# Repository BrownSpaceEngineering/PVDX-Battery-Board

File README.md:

# Battery-Board

Battery subsystem board for PVDX — connects the battery stack, solar cells/solar PCB, heaters, and thermistors.

## Status
- Design phase: fabrication
- Current rev: rev-1.1
- Contributors: Jayla Hsiung, Kelly Lin, Finn Kehoe, Dean Zweiman

## System overview

The Battery Board is primarily structural/routing rather than active. It has no onboard charging or regulation ICs (that logic lives on EPS). Its job is to tie the battery stack into the rest of the power subsystem: routing to the regular (non-perovskite) solar cells and solar PCB, driving the battery heaters, and carrying thermistor signals back for battery temperature monitoring.

**Board sheets:**

- **Heater**: battery heater circuit.
- **Connectors**: harness/pinout for battery, solar, heater, and thermistor connections. These are being hardwired rather than connectorized — the footprints (pad patterns) stay on the board for wire attachment points, but the 3D models are hidden (Show unchecked in Footprint Properties → 3D Models) so they don't appear in the STEP export.

### Repo layout

```
PVDX-Battery-Board/
├── PVDX-Battery-Board.kicad_pro / .kicad_sch / .kicad_pcb
├── fp-lib-table
├── schematics/
│   ├── heater.kicad_sch
│   └── connectors.kicad_sch
├── libs/
│   ├── footprints.pretty/
│   ├── symbols/
│   └── 3d_models/
└── manufacturing/
    └── rev-<N>_<date>/
        ├── gerbers/
        ├── bom/
        └── plots/
```

**Why hardwire instead of connectors:** simplifies the harness at the battery/heater interface and removes a failure point (connector) from a joint that doesn't need to be serviceable in flight. KiCad has no dedicated "exclude from STEP" option, so per-footprint 3D model visibility is the mechanism used to keep the pad pattern without the connector body in mechanical exports.

## Key design notes

- **Thermistor (NXFT15XV103FEAB025):** custom footprint, kept in `libs/footprints.pretty/`. The original vendor export had a stray space in the filename — fixed during the repo reorg.
- **Connector footprints, 3D models hidden:** see above — keep an eye on this after any "Update PCB from Schematic" footprint refresh, which can reset visibility to the library default and re-show the model.
- **`PVDX_BatteryBoard_Board.kicad_sch`** was an orphaned, blank sheet not referenced anywhere in the hierarchy — deleted during the reorg.

## Manufacturing history
| Rev | Date | Notes | Location |
|-----|------|-------|----------|
| 1.1 | 8/22/26 | Current gerber set | `manufacturing/rev-1.1_2026-08-22/` |

## Open items
- Fill in BOM for rev-1.1 (`manufacturing/rev-1.1_2026-08-22/bom/` currently empty)

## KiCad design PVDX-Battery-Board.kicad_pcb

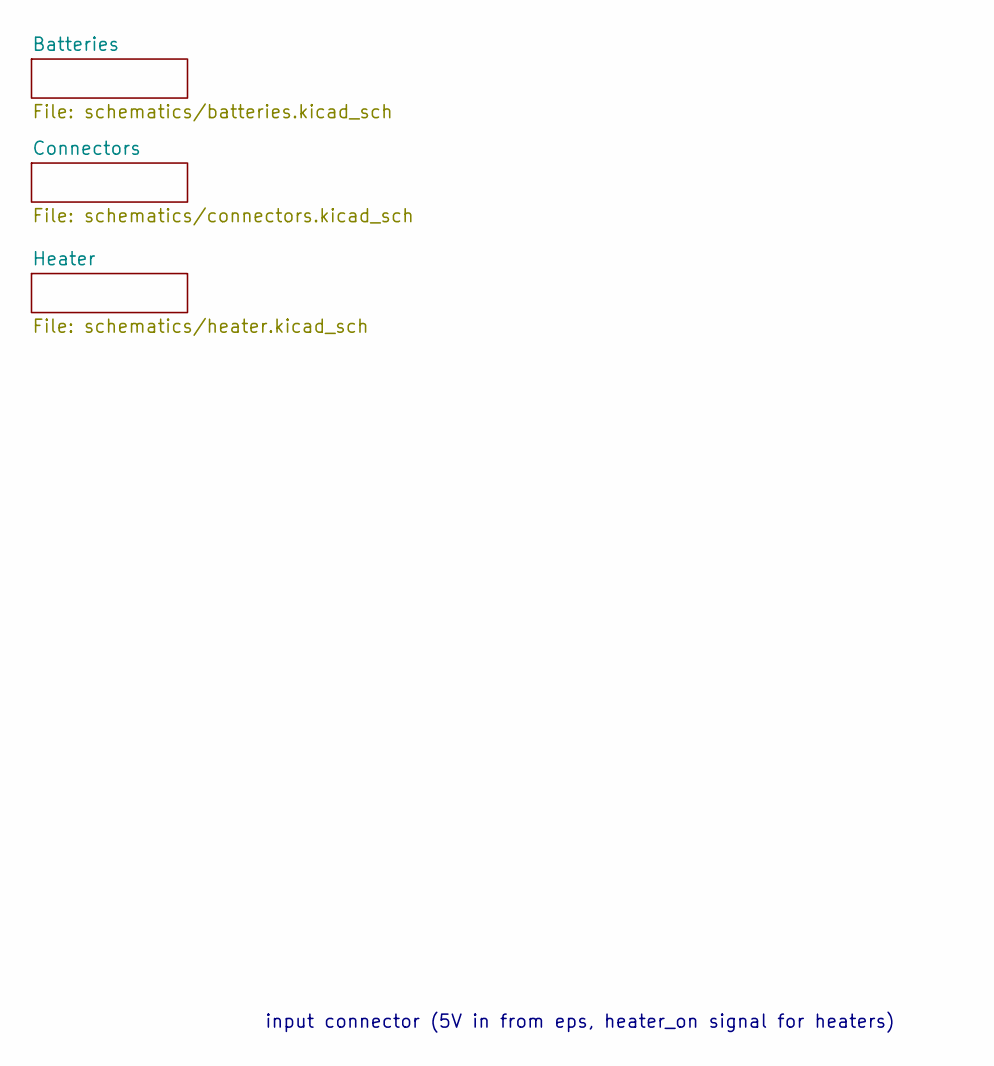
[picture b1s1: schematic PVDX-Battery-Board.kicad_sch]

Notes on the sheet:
input connector (5V in from eps, heater_on signal for heaters)

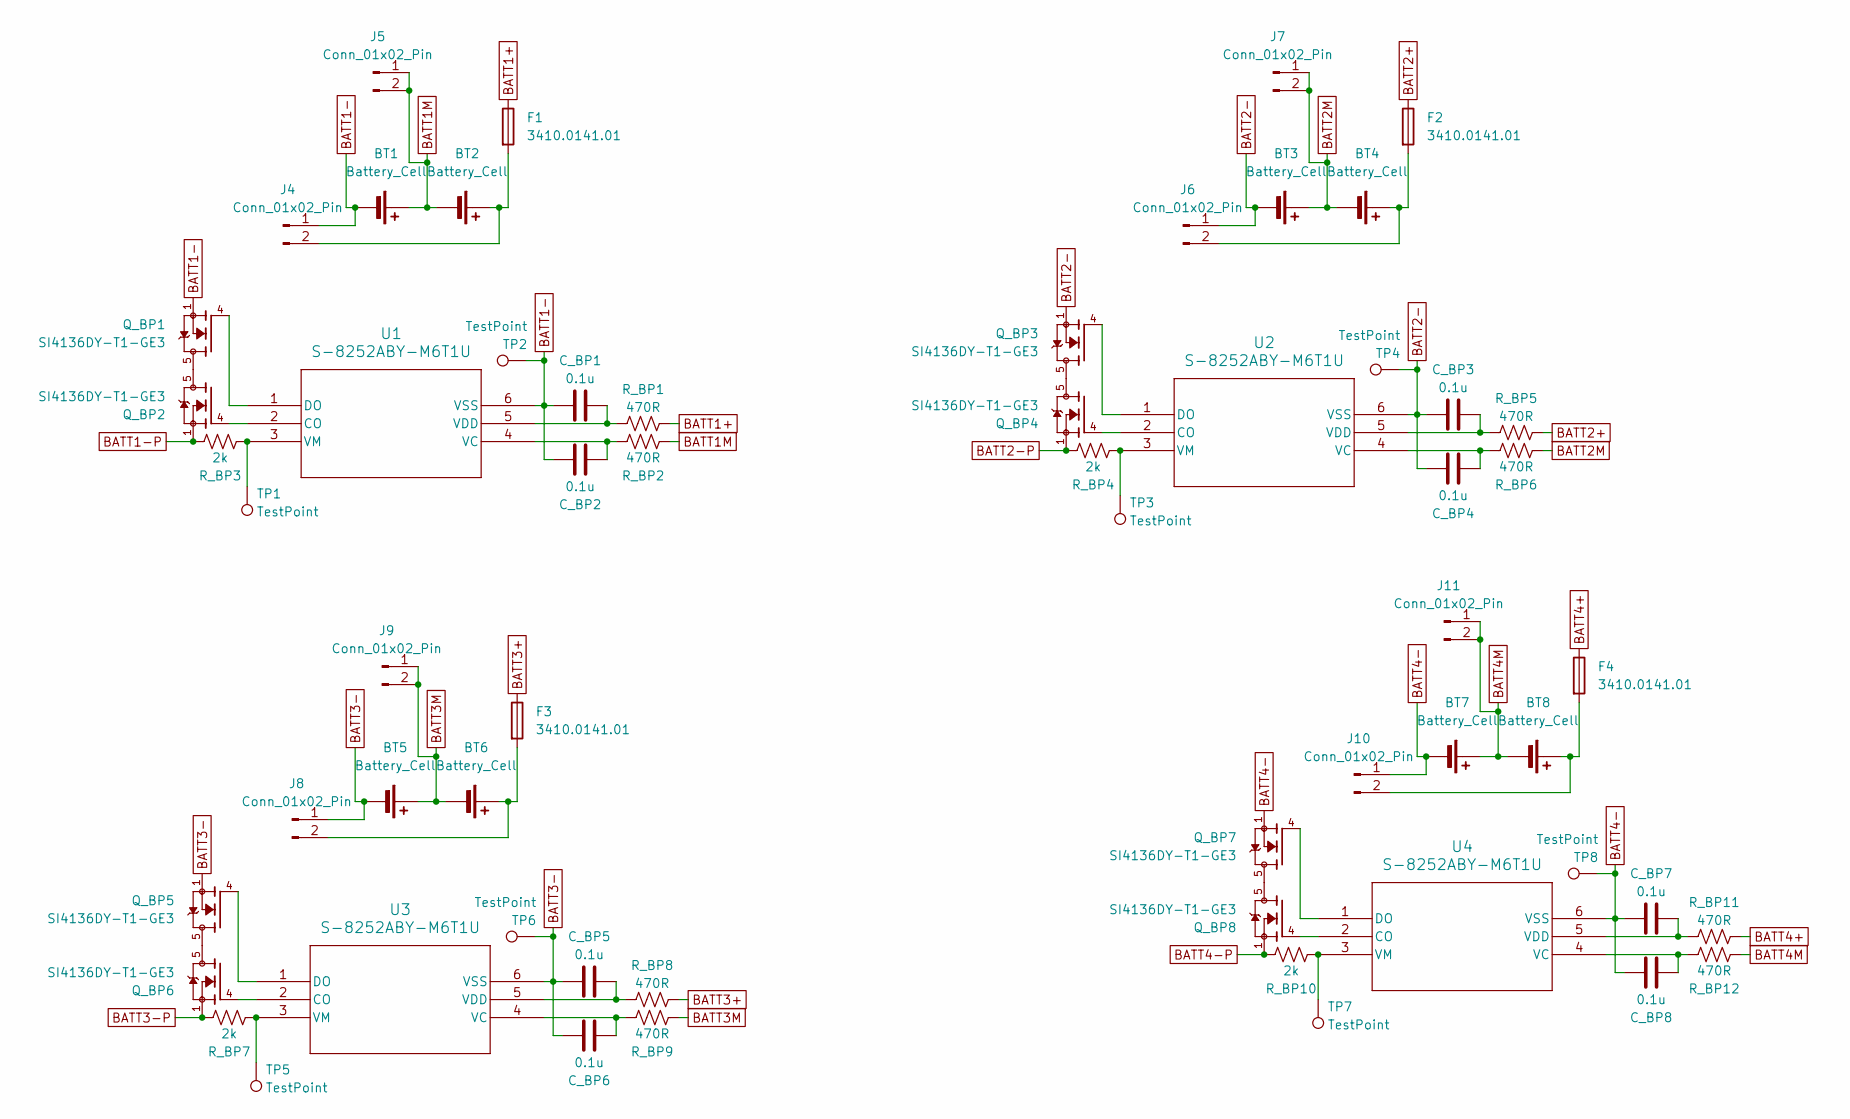
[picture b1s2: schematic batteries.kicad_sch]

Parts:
BT1, BT2, BT3, BT4, BT5, BT6, BT7, BT8: Battery_Cell
C_BP1, C_BP2, C_BP3, C_BP4, C_BP5, C_BP6, C_BP7, C_BP8: 0.1u; C_0603_1608Metric
F1, F2, F3, F4: 3410.0141.01; Fuse_1206_3216Metric
J4, J5, J6, J7, J8, J9, J10, J11: Conn_01x02_Pin; PinSocket_1x02_P2.54mm_Vertical
Q_BP1, Q_BP2, Q_BP3, Q_BP4, Q_BP5, Q_BP6, Q_BP7, Q_BP8: SI4136DY-T1-GE3; SOIC127P600X175-8N; MOUSER_PART_NUMBER 781-SI4136DY-T1-GE3
R_BP1, R_BP2, R_BP5, R_BP6, R_BP8, R_BP9, R_BP11, R_BP12: 470R; R_0603_1608Metric
R_BP3, R_BP4, R_BP7, R_BP10: 2k; R_0603_1608Metric
TP1, TP2, TP3, TP4, TP5, TP6, TP7, TP8: TestPoint; TestPoint_Pad_D1.5mm
U1, U2, U3, U4: S-8252ABY-M6T1U; SOT236-A-PKG_MP006-A-P-SD-2.1_ABY

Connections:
BATT1+: F1.1, R_BP1.2; also elsewhere on the board
BATT1-: BT1.2 (-), C_BP1.1, C_BP2.2, J4.1, Q_BP1.1, Q_BP1.2, Q_BP1.3, TP2.1 (1_1), U1.6 (VSS)
BATT1-P: Q_BP2.1, Q_BP2.2, Q_BP2.3, R_BP3.2; also elsewhere on the board
BATT1M: BT1.1 (+), BT2.2 (-), J5.1, J5.2, R_BP2.1; also elsewhere on the board
BATT2+: F2.1, R_BP5.2; also elsewhere on the board
BATT2-: BT3.2 (-), C_BP3.1, C_BP4.2, J6.1, Q_BP3.1, Q_BP3.2, Q_BP3.3, TP4.1 (1_1), U2.6 (VSS)
BATT2-P: Q_BP4.1, Q_BP4.2, Q_BP4.3, R_BP4.2; also elsewhere on the board
BATT2M: BT3.1 (+), BT4.2 (-), J7.1, J7.2, R_BP6.1; also elsewhere on the board
BATT3+: F3.1, R_BP8.2; also elsewhere on the board
BATT3-: BT5.2 (-), C_BP5.1, C_BP6.2, J8.1, Q_BP5.1, Q_BP5.2, Q_BP5.3, TP6.1 (1_1), U3.6 (VSS)
BATT3-P: Q_BP6.1, Q_BP6.2, Q_BP6.3, R_BP7.2; also elsewhere on the board
BATT3M: BT5.1 (+), BT6.2 (-), J9.1, J9.2, R_BP9.1; also elsewhere on the board
BATT4+: F4.1, R_BP11.2; also elsewhere on the board
BATT4-: BT7.2 (-), C_BP7.1, C_BP8.2, J10.1, Q_BP7.1, Q_BP7.2, Q_BP7.3, TP8.1 (1_1), U4.6 (VSS)
BATT4-P: Q_BP8.1, Q_BP8.2, Q_BP8.3, R_BP10.2; also elsewhere on the board
BATT4M: BT7.1 (+), BT8.2 (-), J11.1, J11.2, R_BP12.1; also elsewhere on the board
unnamed: BT2.1 (+), F1.2, J4.2
unnamed: BT4.1 (+), F2.2, J6.2
unnamed: BT6.1 (+), F3.2, J8.2
unnamed: BT8.1 (+), F4.2, J10.2
unnamed: Q_BP1.5, Q_BP1.6, Q_BP1.7, Q_BP1.8, Q_BP2.5, Q_BP2.6, Q_BP2.7, Q_BP2.8
unnamed: Q_BP3.5, Q_BP3.6, Q_BP3.7, Q_BP3.8, Q_BP4.5, Q_BP4.6, Q_BP4.7, Q_BP4.8
unnamed: Q_BP5.5, Q_BP5.6, Q_BP5.7, Q_BP5.8, Q_BP6.5, Q_BP6.6, Q_BP6.7, Q_BP6.8
unnamed: Q_BP7.5, Q_BP7.6, Q_BP7.7, Q_BP7.8, Q_BP8.5, Q_BP8.6, Q_BP8.7, Q_BP8.8
unnamed: Q_BP2.4, U1.2 (CO)
unnamed: Q_BP1.4, U1.1 (DO)
unnamed: C_BP2.1, R_BP2.2, U1.4 (VC)
unnamed: C_BP1.2, R_BP1.1, U1.5 (VDD)
unnamed: R_BP3.1, TP1.1 (1_1), U1.3 (VM)
unnamed: Q_BP4.4, U2.2 (CO)
unnamed: Q_BP3.4, U2.1 (DO)
unnamed: C_BP4.1, R_BP6.2, U2.4 (VC)
unnamed: C_BP3.2, R_BP5.1, U2.5 (VDD)
unnamed: R_BP4.1, TP3.1 (1_1), U2.3 (VM)
unnamed: Q_BP6.4, U3.2 (CO)
unnamed: Q_BP5.4, U3.1 (DO)
unnamed: C_BP6.1, R_BP9.2, U3.4 (VC)
unnamed: C_BP5.2, R_BP8.1, U3.5 (VDD)
unnamed: R_BP7.1, TP5.1 (1_1), U3.3 (VM)
unnamed: Q_BP8.4, U4.2 (CO)
unnamed: Q_BP7.4, U4.1 (DO)
unnamed: C_BP8.1, R_BP12.2, U4.4 (VC)
unnamed: C_BP7.2, R_BP11.1, U4.5 (VDD)
unnamed: R_BP10.1, TP7.1 (1_1), U4.3 (VM)

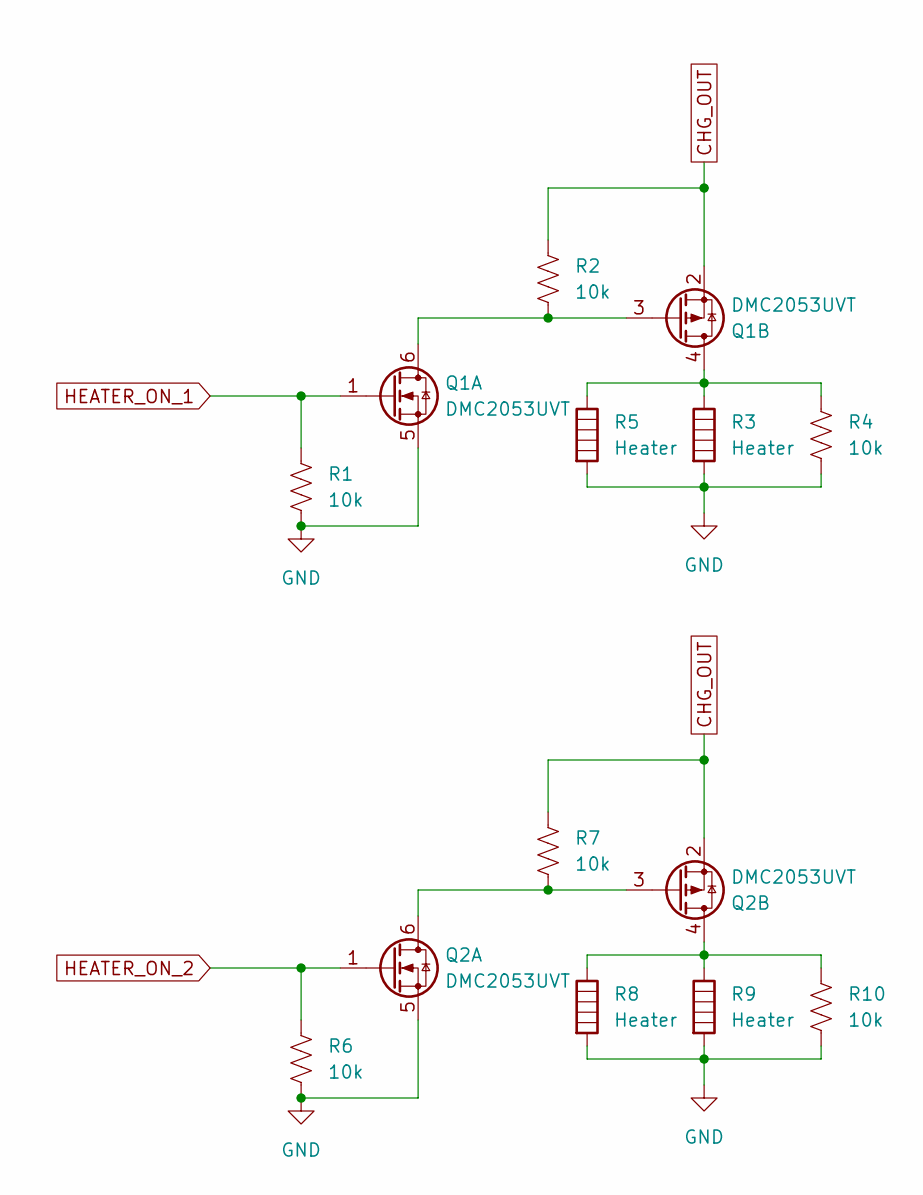
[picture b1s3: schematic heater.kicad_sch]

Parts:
Q1, Q2: DMC2053UVT; TSOT-23-6
R1, R2, R4, R6, R7, R10: 10k; R_0603_1608Metric
R3, R5, R8, R9: Heater; PinHeader_1x02_P2.54mm_Vertical

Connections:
CHG_OUT: Q1.2 (S), Q2.2 (S), R2.1, R7.1; also elsewhere on the board
HEATER_ON_1: Q1.1 (G), R1.1; also elsewhere on the board
HEATER_ON_2: Q2.1 (G), R6.1; also elsewhere on the board
unnamed: Q1.3 (G), Q1.6 (D), R2.2
unnamed: Q1.4 (D), R3.1, R4.1, R5.1
unnamed: Q2.3 (G), Q2.6 (D), R7.2
unnamed: Q2.4 (D), R8.1, R9.1, R10.1
SOLAR_1s_GND: Q1.5 (S), Q2.5 (S), R1.2, R3.2, R4.2, R5.2, R6.2, R8.2, R9.2, R10.2; also elsewhere on the board

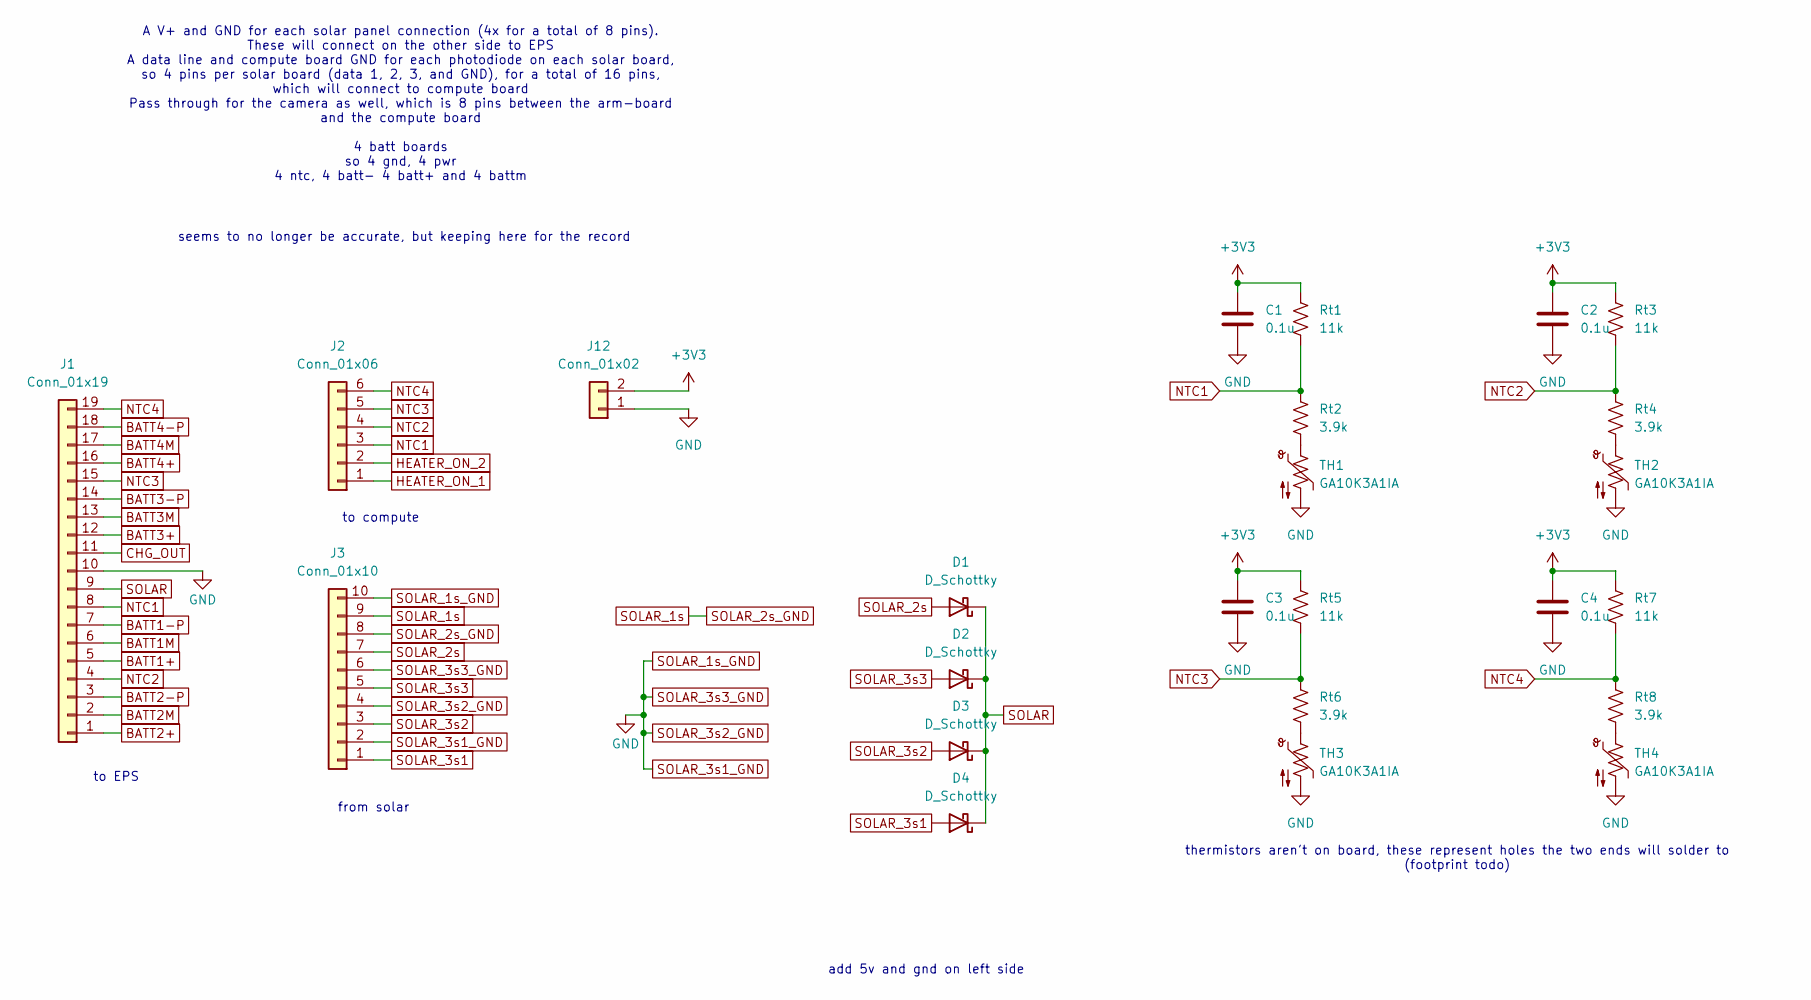
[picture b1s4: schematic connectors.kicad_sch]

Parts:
C1, C2, C3, C4: 0.1u; C_0603_1608Metric
D1, D2, D3, D4: D_Schottky; D_SOD-128; MPN RSX301LAM30TR
J1: Conn_01x19; PinHeader_1x19_P2.54mm_Vertical
J2: Conn_01x06; PinSocket_1x06_P2.54mm_Vertical
J3: Conn_01x10; PinSocket_1x10_P2.54mm_Vertical
J12: Conn_01x02; PinHeader_1x02_P2.54mm_Vertical
Rt1, Rt3, Rt5, Rt7: 11k; R_0603_1608Metric
Rt2, Rt4, Rt6, Rt8: 3.9k; R_0603_1608Metric
TH1, TH2, TH3, TH4: GA10K3A1IA; PinHeader_1x02_P2.54mm_Vertical

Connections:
+3V3: C1.1, C2.1, C3.1, C4.1, J12.2, Rt1.1, Rt3.1, Rt5.1, Rt7.1
BATT1+: J1.5; also elsewhere on the board
BATT1-P: J1.7; also elsewhere on the board
BATT1M: J1.6; also elsewhere on the board
BATT2+: J1.1; also elsewhere on the board
BATT2-P: J1.3; also elsewhere on the board
BATT2M: J1.2; also elsewhere on the board
BATT3+: J1.12; also elsewhere on the board
BATT3-P: J1.14; also elsewhere on the board
BATT3M: J1.13; also elsewhere on the board
BATT4+: J1.16; also elsewhere on the board
BATT4-P: J1.18; also elsewhere on the board
BATT4M: J1.17; also elsewhere on the board
CHG_OUT: J1.11; also elsewhere on the board
HEATER_ON_1: J2.1; also elsewhere on the board
HEATER_ON_2: J2.2; also elsewhere on the board
NTC1: J1.8, J2.3, Rt1.2, Rt2.1
NTC2: J1.4, J2.4, Rt3.2, Rt4.1
NTC3: J1.15, J2.5, Rt5.2, Rt6.1
NTC4: J1.19, J2.6, Rt7.2, Rt8.1
unnamed: Rt2.2, TH1.1
unnamed: Rt4.2, TH2.1
unnamed: Rt6.2, TH3.1
unnamed: Rt8.2, TH4.1
SOLAR: D1.1 (K), D2.1 (K), D3.1 (K), D4.1 (K), J1.9
SOLAR_1s: J3.8, J3.9
SOLAR_1s_GND: C1.2, C2.2, C3.2, C4.2, J1.10, J3.2, J3.4, J3.6, J3.10, J12.1, TH1.2, TH2.2, TH3.2, TH4.2; also elsewhere on the board
SOLAR_2s: D1.2 (A), J3.7
SOLAR_3s1: D4.2 (A), J3.1
SOLAR_3s2: D3.2 (A), J3.3
SOLAR_3s3: D2.2 (A), J3.5

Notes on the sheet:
seems to no longer be accurate, but keeping here for the record
A V+ and GND for each solar panel connection (4x for a total of 8 pins). These will connect on the other side to EPS A data line and compute board GND for each photodiode on each solar board, so 4 pins per solar board (data 1, 2, 3, and GND), for a total of 16 pins, which will connect to compute bo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
from solar
to EPS
thermistors aren't on board, these represent holes the two ends will solder to (footprint todo)
add 5v and gnd on left side
to compute

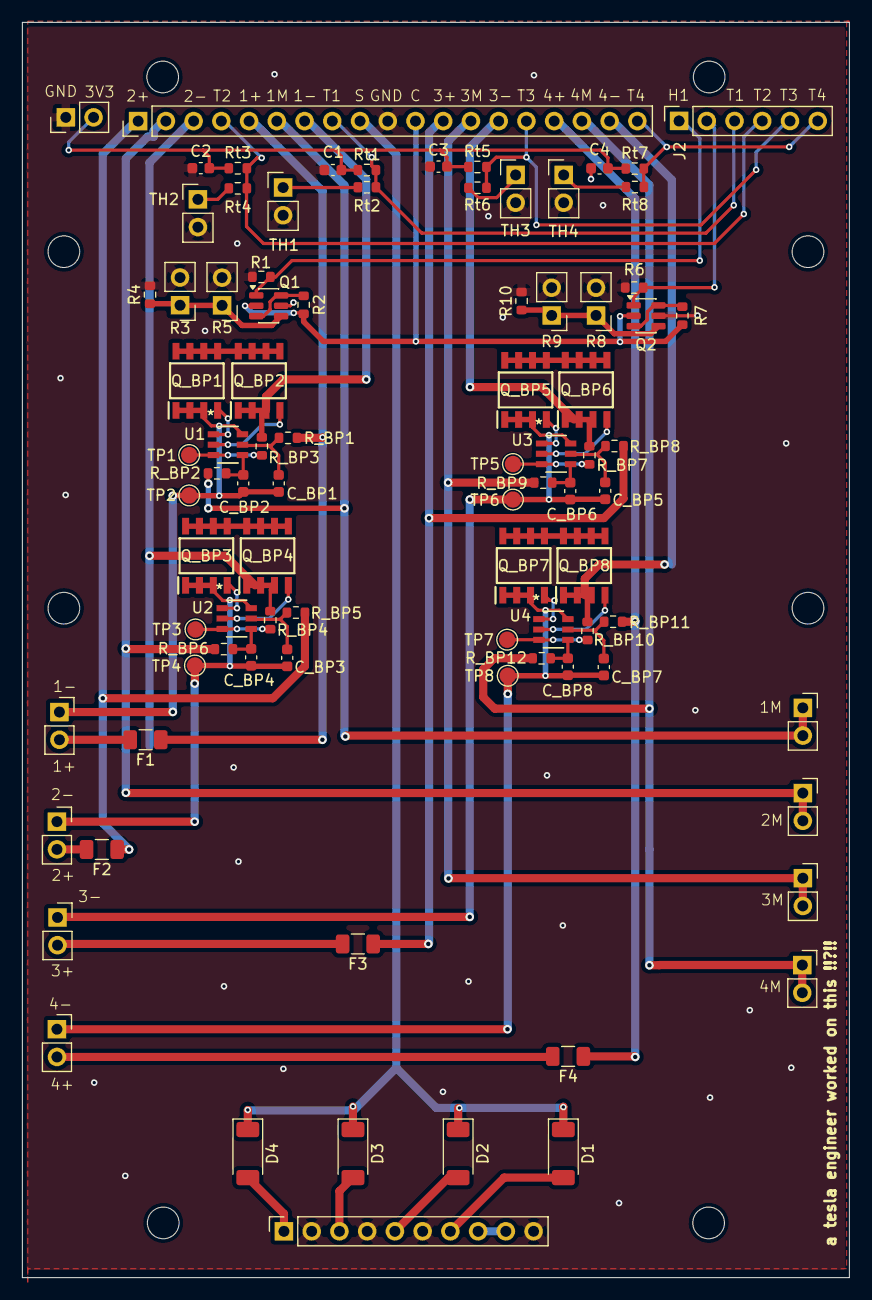
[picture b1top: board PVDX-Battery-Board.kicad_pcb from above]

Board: 2 copper layers, 75.7 x 115.0 mm, 88 parts (0 on the bottom side), 67 nets.

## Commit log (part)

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2026-04-27 connectors
2026-04-28 added heater schematic
2026-05-01 added solar connectors schematic
2026-05-03 added second heater to heater schematic
